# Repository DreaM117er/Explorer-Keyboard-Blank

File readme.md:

# Explorer Keyboard Blank 探索者3號

|4x6 v1|5x6 v1|
|--|--|
|||
|||
|||
|||

## 開發者前言

Plank，是大部分人入坑人體工學鍵盤時最常接觸到的鍵盤，因為它方且正，許多的人體工學鍵盤的基礎都是在這個方正的鍵盤上延伸；

Blank，翻譯成中文的意思為空白。結合了Plank所需要的基礎，進而把鍵盤拓展成可分離的版本，你可以只使用單側、也可以使用兩側、可以在你需要的那一側加裝自己需要的特殊元件，也可以將元件放置在手的左或右側...

並且支援Kailh矮軸Choc v1、v2、Gateron矮軸GLP雙熱插拔，選擇自己所喜歡的按鍵軸及鍵帽——

因此將它歸為探索者系列，稱之為Blank，稱之為3號。

## 靈感來源

- 我只是想做一把簡單的鍵盤。
- 開發上一把鍵盤時發現我最多只需要2顆旋鈕。
- 不想思考太多。
- 突然想到自己曾經在beekeeb上看到Cirque 40mm的觸控板模組。
- 試試看做個能同時翻面支援的電路板好了。

如果想知道完整的開發過程，請詳細閱讀[開發日誌](log.md)中的內文。

## 前置作業

### 電路板

||4x6 v1|5x6 v1|
|--|--|--|
|正面|||
|背面|||

### 外殼

||4x6 v1|5x6 v1|
|--|--|--|
|底板|||
|定位板|||
|擋板A|||
|擋板B|||
|擋板C|||
|MCU擋板|||

### 會使用到的工具

|名稱|備註|詳細說明|
|--|--|--|
|電烙鐵|-|焊錫、助焊劑等相關工具組|
|防靜電鑷子|-|用於微調貼片元件使用|
|金屬鑷子|-|用於測試電路用|
|加熱台|選配|用於固定貼片元件使用|
|熱風槍|選配|用於固定貼片元件使用|

### 使用材料（單側組裝）

|4x6 v1|5x6 v1|
|--|--|
|||
|||

|-|名稱|數量|數量|備註|詳細說明|
|--|--|--|--|--|--|
|||**4x6**|**5x6**|||
||PCB|1|-|-|雙面通用，`1.6mm`厚度|
||外殼|1|-|-|左右通用，`1.6mm`厚度|
|*|定位板|1|-|-|左右通用，`1.2mm`厚度|
|*|`ProMicro`|1|-|同腳MCU都可|推薦使用`RP2040`版本|
|*|二極體 `1N4148`|25|31|-|`SMD`貼片式|
|*|熱插拔座|24|30|`Choc`、`GLP`|二選一|
||`2pin`輕觸開關|1|-|-|-|
|*|M2螺絲墊片|6|-|-|穩固鍵盤結構使用|
||M2x`8mm` 扁頭螺絲|6|-|-|-|
||M2x`6mm` 扁頭螺絲|8|-|-|-|
||M2x`4mm` 扁頭螺絲|4|6|-|-|
||M2x`3mm` 扁頭螺絲|6|8|-|-|
||M2螺母|10|-|-|-|
||M2x`8mm` 雙通銅柱|2|4|-|-|
||M2x`5mm` 雙通銅柱|8|-|-|-|
||`ø8mm` `H1mm` 矽膠自黏腳貼|4|-|-|-|
|*|`Cirque` `40mm`觸控板|1|-|選配|推薦帶`曲面`之版本|
||`FFC` `12pin` 排線連接座|1|-|選配|如有`I2C轉接座`可不需使用|
|*|`FFC` `12pin` 軟排線|1|-|選配|`正對正接口`、`50mm`長即可|
|*|`4.7K` 上拉電阻|2|-|選配|`THT`直插式，安裝觸控板才需要使用|
|*|旋鈕編碼器|1|-|選配|`EC11`、`EC12`擇一使用；`L：10mm`、`A：4.5-5.0mm`，推薦`半軸` `D型`|
|*|旋鈕編碼器帽蓋|1|-|選配|`ø39mm`、`軸孔深4.5mm`特製版，推薦3D列印|
||`3.5mm` `TRRS`座|1|2|選配|單側安裝不需使用|

探索者3號支援各大網路商家販售的Cirque 40mm的觸控板模組拓展包，裡頭基本一應俱全，可考慮直接從通路購買：

- [40mm Cirque GlidePoint Circle Trackpad Module DIY Kit for Split Mechanical Keyboard](https://shop.beekeeb.com/product/40mm-cirque-glidepoint-circle-trackpad-module-diy-kit-for-split-mechanical-keyboard/)
- [GlidePoint Cirque Trackpad TM040040 TM035035](https://keycapsss.com/keyboard-parts/parts/211/glidepoint-cirque-trackpad-tm040040-tm035035)

### 注意事項

1. 上面表列材料表為`單片電路板安裝使用`。
2. 列表前標記`*`的材料為極度重要之零組件，請留意是否準備齊全，參照如下：

    - 二極體`1N4148`及`熱插拔座`請務必準備齊全，否則鍵盤會無法正常使用。
    - 旋鈕`編碼器`需搭配`帽蓋`一起安裝。
    - Crique 40mm`觸控板`需搭配`4.7k上拉電阻`、`12pin軟排線`安裝，缺一不可，請特別留意。
    - `M2螺絲墊片`務必準備齊全，有關鍵盤整體的`結構`，務必安裝上去。
 
3. 機械鍵軸務必跟隨熱插拔座的規格進行購買，因為`Choc跟GLP規格不相容`。
4. 使用電烙鐵時務必留意`環境通風`、`用電安全`及`燙傷預防`。
5. 在進入組裝環節之前，務必先將beekeeb及Keycapsss的組裝流程看過一輪：

    - [Cirque Trackpad i2c on Corne Keyboard Build Log](https://beekeeb.com/cirque-trackpad-i2c-on-corne-keyboard/)。
    - [GlidePoint Cirque Trackpad with Adapter PCB](https://keycapsss.com/help/cirque-trackpad/#spi-or-i2c)。

環境及材料都準備完畢之後，就可以開始進入[組裝環節](guide.md)了。

## 無私的感謝

### 工具軟體
- [KiCAD](https://www.kicad.org/) version `7.0.5`。
- [Autodesk Fusion](https://www.autodesk.com/products/fusion-360/free-trial)。
- [QMK](https://qmk.fm/)、[VIAL](https://get.vial.today/)。

### 規格書
- [TM040040 Trackpad](spc/TM040040.pdf)。
- [Resistor_THT](spc/Resistor_THT.png)。
- [molex 781271110 0.5 FPC CONN.](spc/FPC-Conn-781271110.pdf)。
- ALPS [EC11](<spc/Rotray Encoder EC11.pdf>)、[EC12E](<spc/Rotray Encoder EC12E.PDF>)。

### 商家及廠家
- [太豪股份有限公司](https://www.tai-hao.com/tw/)。
- [凱華電子有限公司](http://www.kailh.com/index.html)。
- [nuphy](https://nuphy.com/)及[Gateron](https://www.gateron.co/)。
- [beekeeb](https://shop.beekeeb.com/)。
- [Keycapsss](https://keycapsss.com/)。
- [JLCPCB](https://jlcpcb.com/)。

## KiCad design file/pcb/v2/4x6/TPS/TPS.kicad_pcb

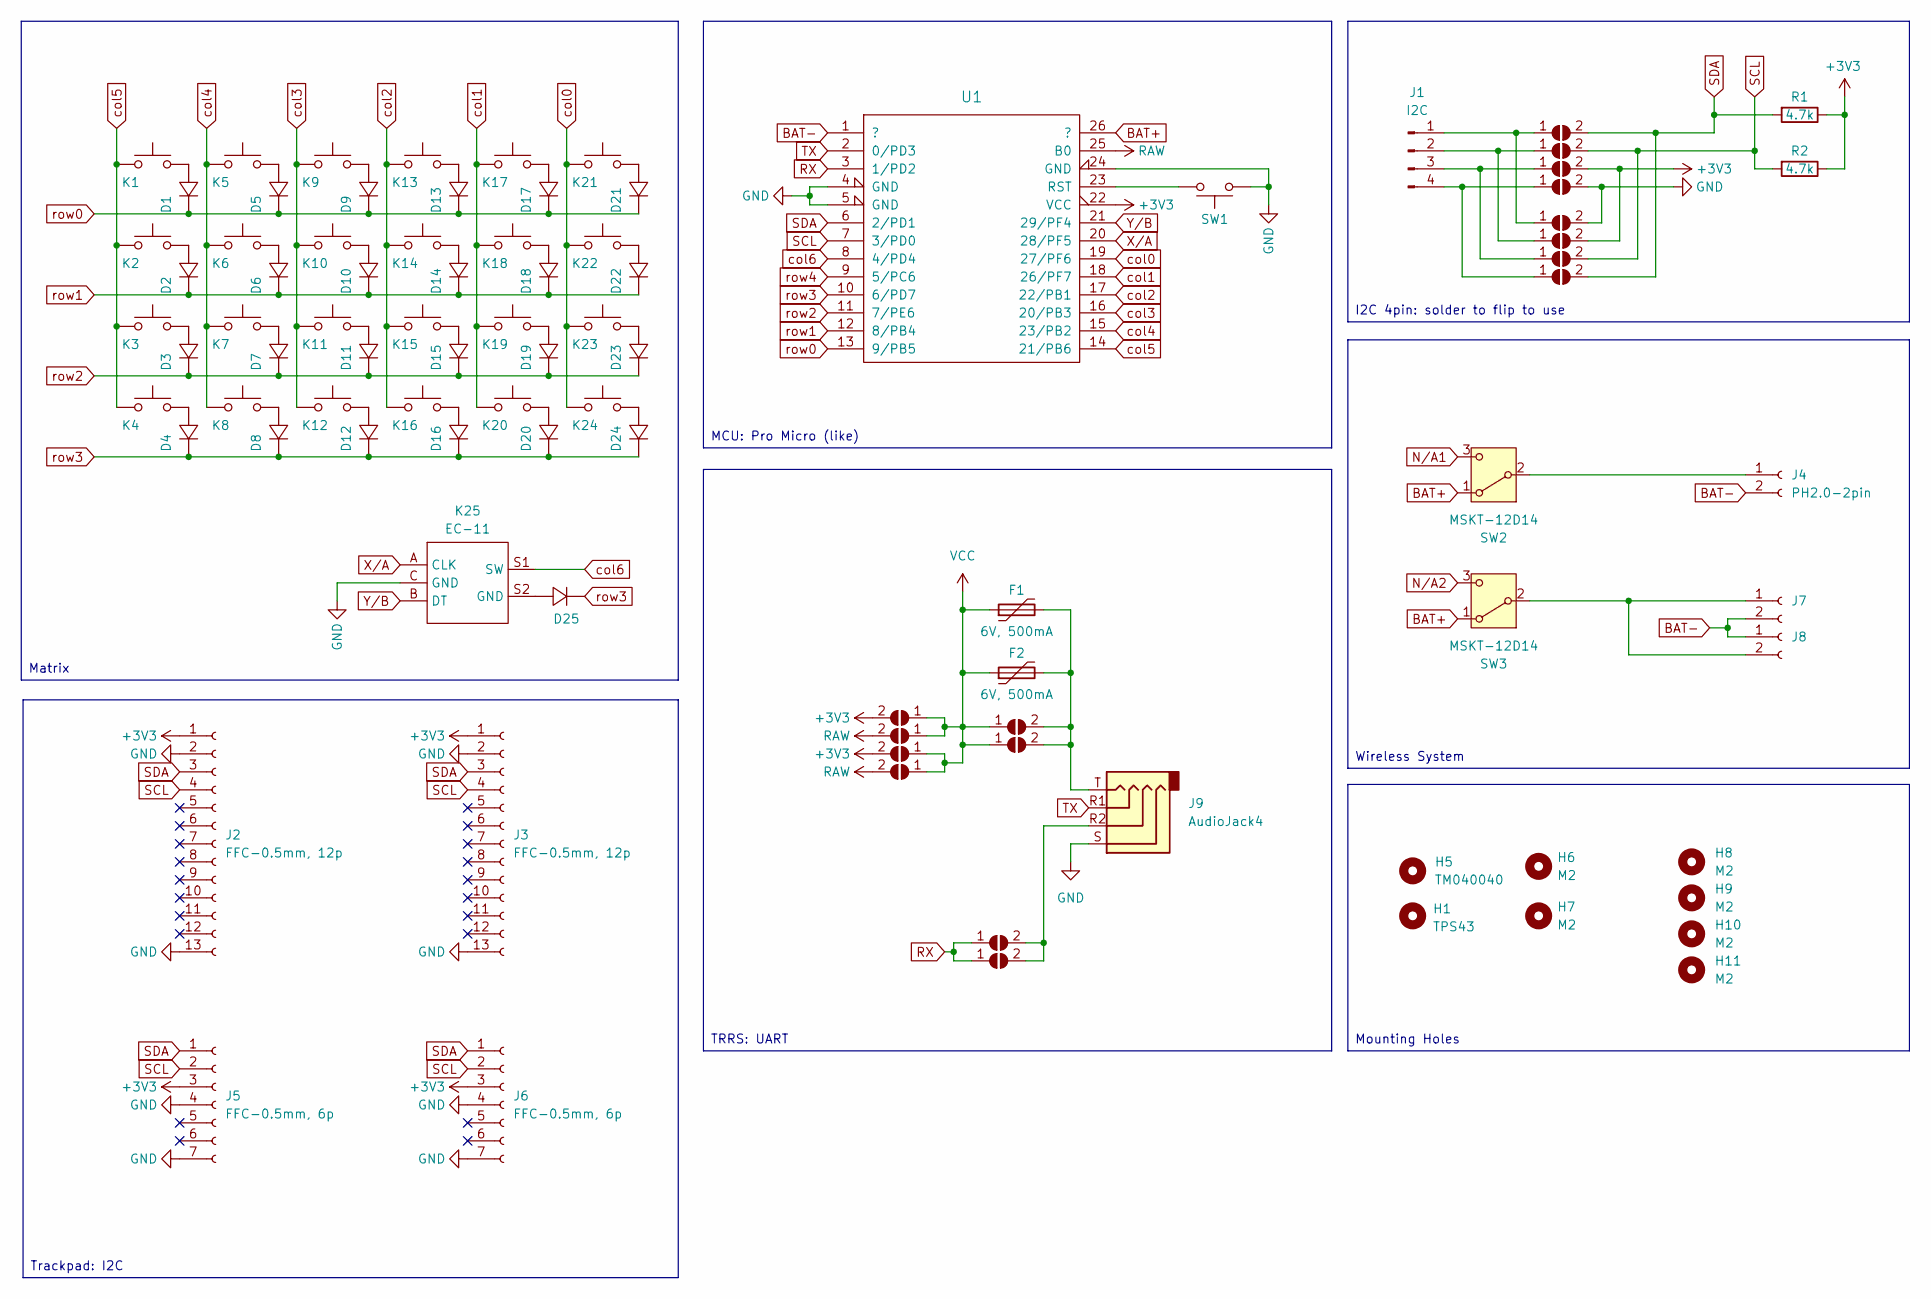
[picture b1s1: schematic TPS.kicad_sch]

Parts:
D1, D2, D3, D4, D5, D6, D7, D8, D9, D10, D11, D12, D13, D14, D15, D16, D17, D18, D19, D20, D21, D22, D23, D24, D25: 1N4148_SMD; D_SOD-123_handsolder_dual
F1, F2: 6V, 500mA; Fuse_0805_2012Metric
H1: TPS43; Azoteq_TPS43_201A_S
H5: TM040040; Trackpad_Cirque_TM040040
H6, H7, H8, H9, H10, H11: M2; MountingHole_2.2mm_M2
J1: I2C; PinHeader_1x04_P2.54mm_Vertical
J2, J3: FFC-0.5mm, 12p; Hirose_FH12-12S-0.5SH_1x12-1MP_P0.50mm_Horizontal
J4: PH2.0-2pin; JST_PH_S2B-PH-K_1x02_P2.00mm_Horizontal_dual
J5, J6: FFC-0.5mm, 6p; Hirose_FH12-6S-0.5SH_1x06-1MP_P0.50mm_Horizontal
J7, J8: PinHeader_1x02_P2.54mm_Vertical
J9: AudioJack4; TRRS-PJ-320A, dual side x2_3rd
JP1, JP2, JP3, JP4: PWR1; SolderJumper-2_P1.3mm_Open_Pad1.0x1.5mm
JP5, JP6, JP7, JP8, JP9, JP10, JP11, JP12: PWR1; SolderJumper-2_P1.3mm_Open_RoundedPad1.0x1.5mm
JP13, JP14: RX; SolderJumper-2_P1.3mm_Open_RoundedPad1.0x1.5mm
JP15, JP16: VCC; SolderJumper-2_P1.3mm_Open_Pad1.0x1.5mm
K1, K2, K3, K4, K5, K6, K7, K8, K9, K10, K11, K12, K13, K14, K15, K16, K17, K18, K19, K20, K21, K22, K23, K24: SW_Push; SW_Hotswap_KLP12_GLP3.0_MX_Plated_1.00u_Dualside
K25: EC-11; RotaryEncoder_EC11
R1, R2: 4.7k; R_Axial_DIN0204_L3.6mm_D1.6mm_P7.62mm_Horizontal
SW1: SW_Push; ResetSW_1side
SW2, SW3: MSKT-12D14; SW_SPDT_MSKT-12D14_SMD_dual
U1: MCU_ProMicro_13p; MCU_ProMicro_13p_dual

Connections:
+3V3: J2.1, J3.1, J5.3, J6.3, JP1.2 (B), JP3.2 (B), JP7.2 (B), JP10.2 (B), R1.1, R2.1, U1.22 (VCC)
BAT+: SW2.1 (A), SW3.1 (A), U1.26 (?)
BAT-: J4.2, J7.2, J8.1, U1.1 (?)
GND: J2.2, J2.13, J3.2, J3.13, J5.4, J5.7, J6.4, J6.7, J9.S, JP8.2 (B), JP9.2 (B), K25.C (GND), SW1.1, U1.4 (GND), U1.5 (GND), U1.24 (GND)
unnamed: D1.2, K1.2
unnamed: D2.2, K2.2
unnamed: D3.2, K3.2
unnamed: D4.2, K4.2
unnamed: D5.2, K5.2
unnamed: D6.2, K6.2
unnamed: D7.2, K7.2
unnamed: D8.2, K8.2
unnamed: D9.2, K9.2
unnamed: D10.2, K10.2
unnamed: D11.2, K11.2
unnamed: D12.2, K12.2
unnamed: D13.2, K13.2
unnamed: D14.2, K14.2
unnamed: D15.2, K15.2
unnamed: D16.2, K16.2
unnamed: D17.2, K17.2
unnamed: D18.2, K18.2
unnamed: D19.2, K19.2
unnamed: D20.2, K20.2
unnamed: D21.2, K21.2
unnamed: D22.2, K22.2
unnamed: D23.2, K23.2
unnamed: D24.2, K24.2
unnamed: D25.2, K25.S2 (GND)
unnamed: J1.1, JP5.1 (A), JP9.1 (A)
unnamed: J1.2, JP6.1 (A), JP10.1 (A)
unnamed: J1.3, JP7.1 (A), JP11.1 (A)
unnamed: J1.4, JP8.1 (A), JP12.1 (A)
unnamed: J4.1, SW2.2 (B)
unnamed: J7.1, J8.2, SW3.2 (B)
unnamed: J9.R2, JP13.2 (B), JP14.2 (B)
unnamed: F1.2, F2.2, J9.T, JP15.2 (B), JP16.2 (B)
unnamed: SW1.2, U1.23 (RST)
N/A1: SW2.3 (C)
N/A2: SW3.3 (C)
RAW: JP2.2 (B), JP4.2 (B), U1.25 (B0)
RX: JP13.1 (A), JP14.1 (A), U1.3 (1/PD2)
SCL: J2.4, J3.4, J5.2, J6.2, JP6.2 (B), JP11.2 (B), R2.2, U1.7 (3/PD0)
SDA: J2.3, J3.3, J5.1, J6.1, JP5.2 (B), JP12.2 (B), R1.2, U1.6 (2/PD1)
TX: J9.R1, U1.2 (0/PD3)
VCC: F1.1, F2.1, JP1.1 (A), JP2.1 (A), JP3.1 (A), JP4.1 (A), JP15.1 (A), JP16.1 (A)
X/A: K25.A (CLK), U1.20 (28/PF5)
Y/B: K25.B (DT), U1.21 (29/PF4)
col0: K21.1, K22.1, K23.1, K24.1, U1.19 (27/PF6)
col1: K17.1, K18.1, K19.1, K20.1, U1.18 (26/PF7)
col2: K13.1, K14.1, K15.1, K16.1, U1.17 (22/PB1)
col3: K9.1, K10.1, K11.1, K12.1, U1.16 (20/PB3)
col4: K5.1, K6.1, K7.1, K8.1, U1.15 (23/PB2)
col5: K1.1, K2.1, K3.1, K4.1, U1.14 (21/PB6)
col6: K25.S1 (SW), U1.8 (4/PD4)
row0: D1.1, D5.1, D9.1, D13.1, D17.1, D21.1, U1.13 (9/PB5)
row1: D2.1, D6.1, D10.1, D14.1, D18.1, D22.1, U1.12 (8/PB4)
row2: D3.1, D7.1, D11.1, D15.1, D19.1, D23.1, U1.11 (7/PE6)
row3: D4.1, D8.1, D12.1, D16.1, D20.1, D24.1, D25.1, U1.10 (6/PD7)
row4: U1.9 (5/PC6)

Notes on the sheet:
I2C 4pin: solder to flip to use
Trackpad: I2C
Mounting Holes
TRRS: UART
Wireless System
MCU: Pro Micro (like)
Matrix

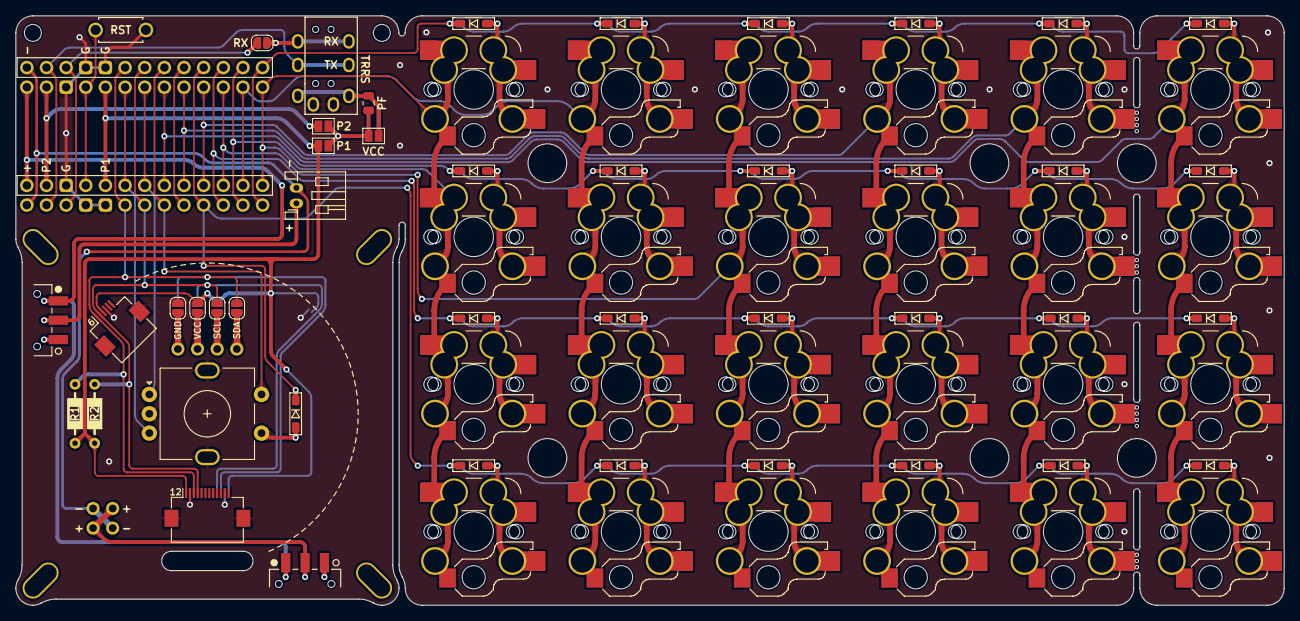
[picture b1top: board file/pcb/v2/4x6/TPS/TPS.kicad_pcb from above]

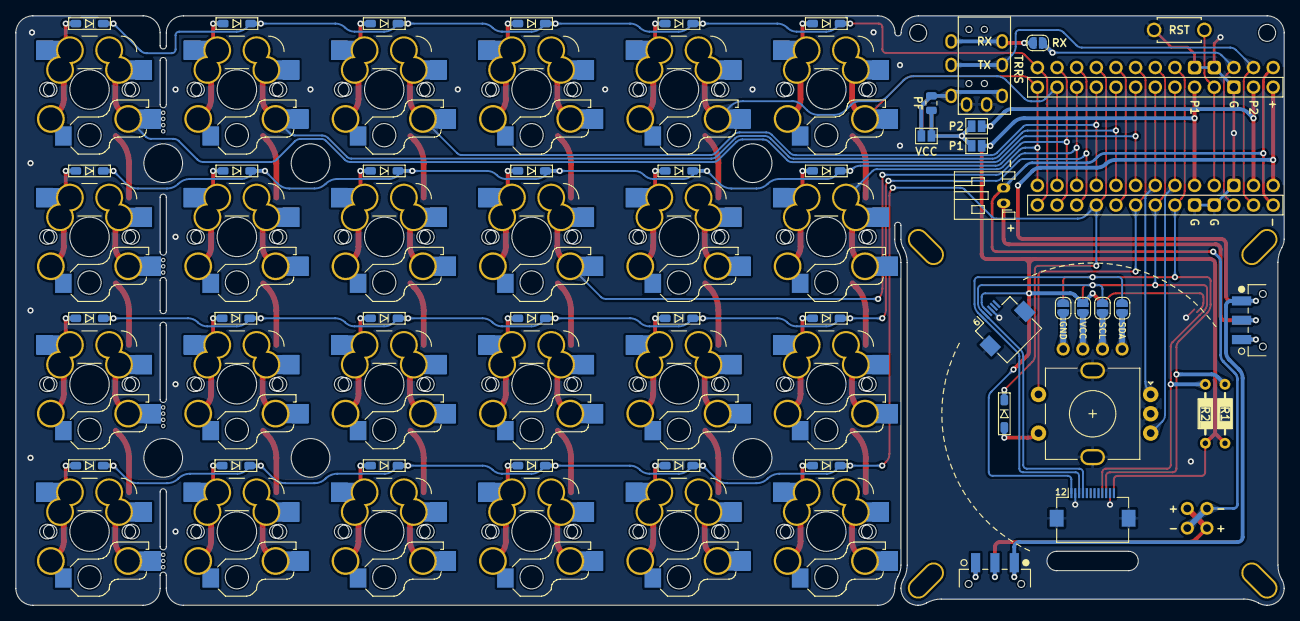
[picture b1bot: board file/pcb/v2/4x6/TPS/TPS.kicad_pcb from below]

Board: 2 copper layers, 164.0 x 76.2 mm, 95 parts (12 on the bottom side), 57 nets.

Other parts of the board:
H14, H15, H16, H17: edge; Breakaway_Tabs_2

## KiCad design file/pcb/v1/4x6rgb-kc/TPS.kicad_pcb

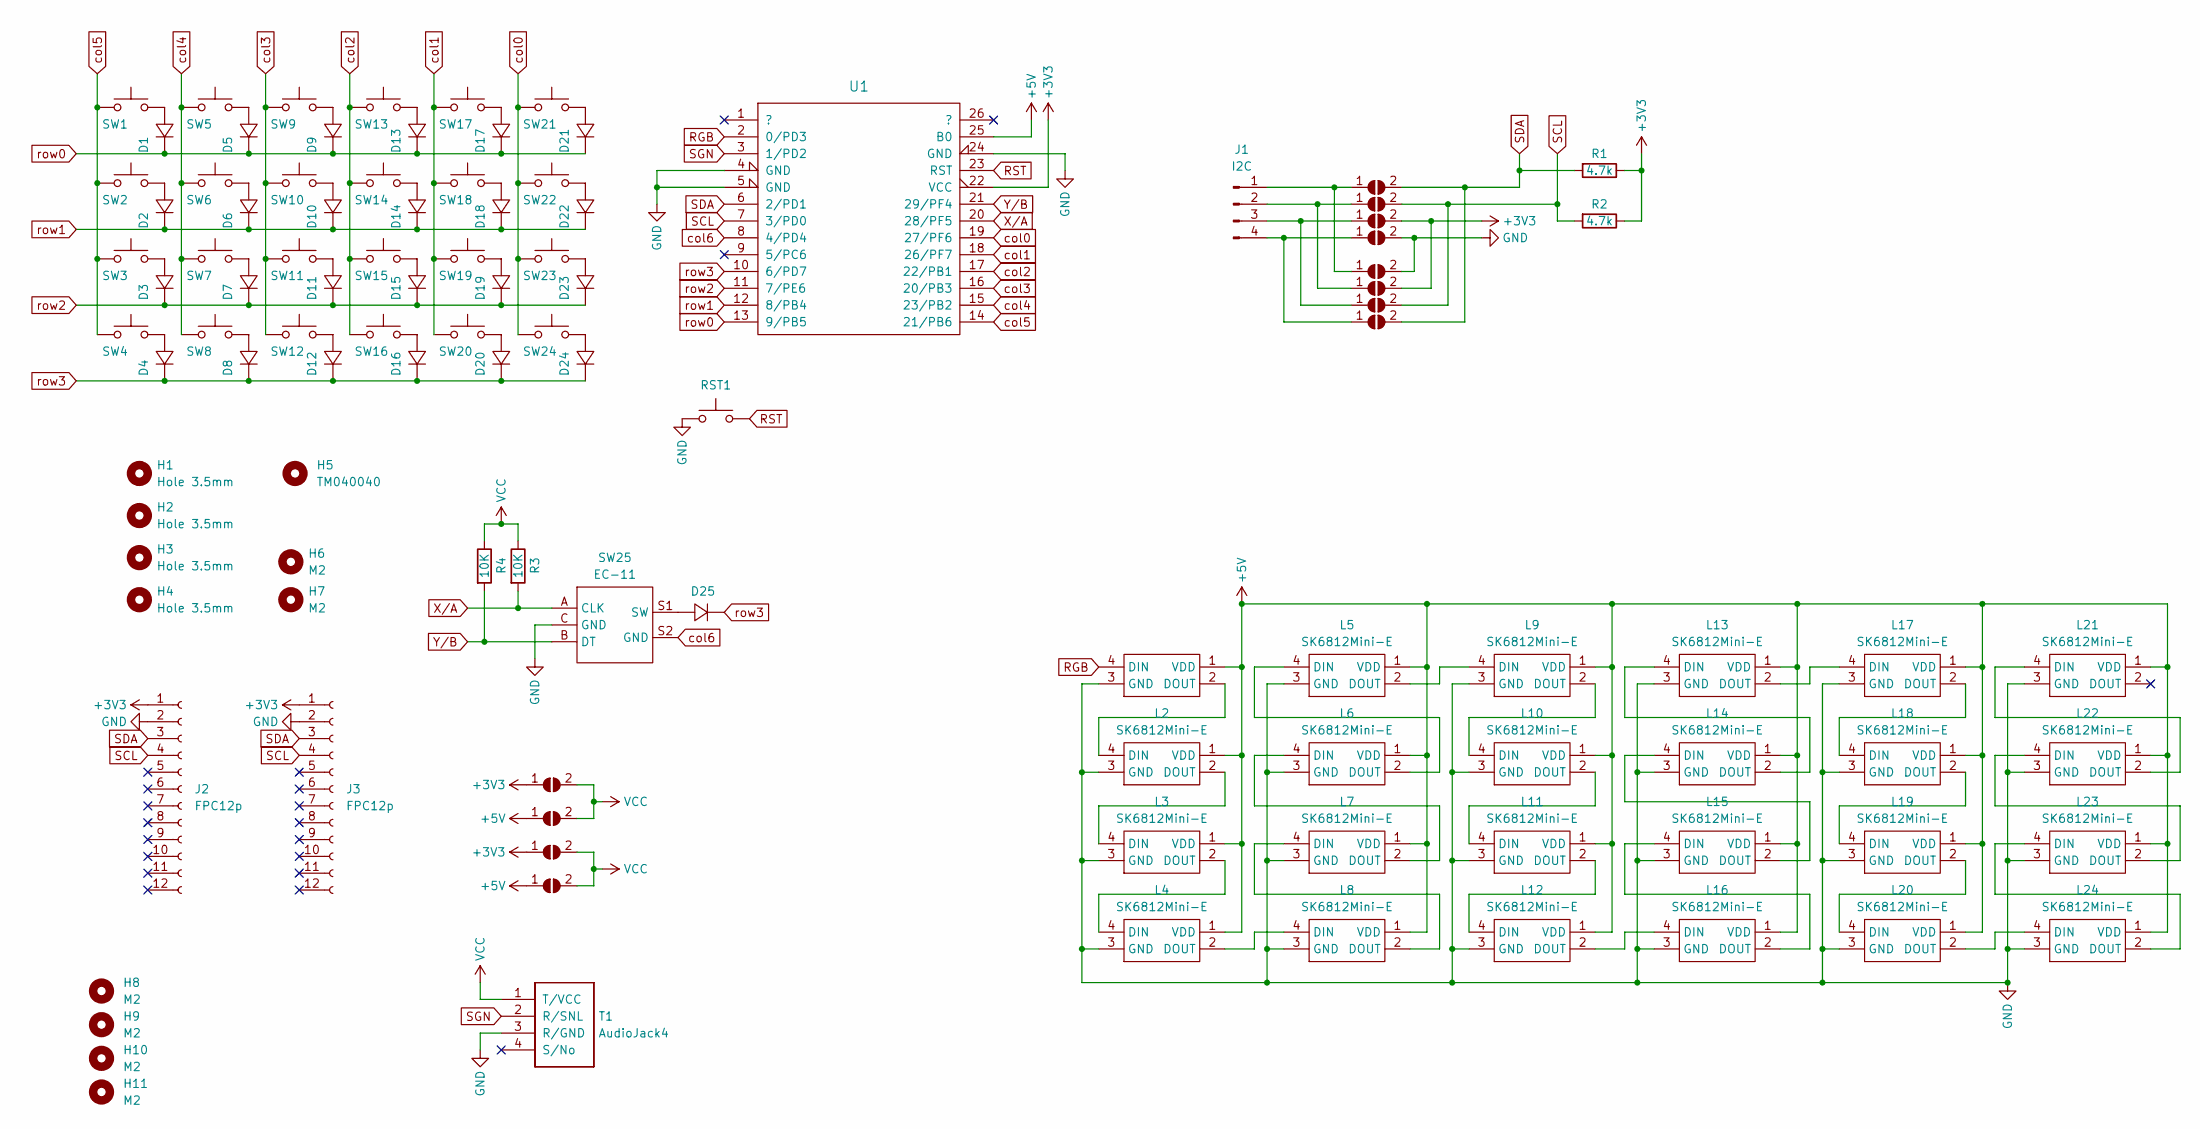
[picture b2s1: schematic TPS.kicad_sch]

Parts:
D1, D2, D3, D4, D5, D6, D7, D8, D9, D10, D11, D12, D13, D14, D15, D16, D17, D18, D19, D20, D21, D22, D23, D24, D25: 1N4148_SMD; D_SOD-123_dual
H1, H2, H3, H4: Hole 3.5mm; MountingHole_3.5mm
H5: TM040040; Trackpad_Cirque_TM040040
H6, H7, H8, H9, H10, H11: M2; MountingHole_2.2mm_M2
J1: I2C; PinHeader_1x04_P2.54mm_Vertical
J2, J3: FPC12p; Hirose_FH12-12S-0.5SH_1x12-1MP_P0.50mm_Horizontal
JP1, JP2, JP3, JP4: PWR1; SolderJumper-2_P1.3mm_Open_Pad1.0x1.5mm
JP5, JP6, JP7, JP8, JP9, JP10, JP11, JP12: PWR1; SolderJumper-2_P1.3mm_Open_RoundedPad1.0x1.5mm
L1, L2, L3, L4, L5, L6, L7, L8, L9, L10, L11, L12, L13, L14, L15, L16, L17, L18, L19, L20, L21, L22, L23, L24: SK6812Mini-E; LED_SK6812MINI-E_dual
R1, R2: 4.7k; R_Axial_DIN0204_L3.6mm_D1.6mm_P7.62mm_Horizontal
R3, R4: 10K; R_Axial_DIN0204_L3.6mm_D1.6mm_P7.62mm_Horizontal
RST1: SW_Push; ResetSW_1side
SW1, SW2, SW3, SW4, SW5, SW6, SW7, SW8, SW9, SW10, SW11, SW12, SW13, SW14, SW15, SW16, SW17, SW18, SW19, SW20, SW21, SW22, SW23, SW24: SW_Push; SW_Choc_KLP12_Hotswap_1.00u_dual
SW25: EC-11; RotaryEncoder_EC11
T1: AudioJack4; TRRS-PJ-320A, dual side x2
U1: MCU_ProMicro_13p; MCU_ProMicro_13p_dual

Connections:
+3V3: J2.1, J3.1, JP1.1 (A), JP3.1 (A), JP7.2 (B), JP10.2 (B), R1.1, R2.1, U1.22 (VCC)
+5V: JP2.1 (A), JP4.1 (A), L1.1 (VDD), L2.1 (VDD), L3.1 (VDD), L4.1 (VDD), L5.1 (VDD), L6.1 (VDD), L7.1 (VDD), L8.1 (VDD), L9.1 (VDD), L10.1 (VDD), L11.1 (VDD), L12.1 (VDD), L13.1 (VDD), L14.1 (VDD), L15.1 (VDD), L16.1 (VDD), L17.1 (VDD), L18.1 (VDD), L19.1 (VDD), L20.1 (VDD), L21.1 (VDD), L22.1 (VDD), L23.1 (VDD), L24.1 (VDD), U1.25 (B0)
GND: J2.2, J3.2, JP8.2 (B), JP9.2 (B), L1.3 (GND), L2.3 (GND), L3.3 (GND), L4.3 (GND), L5.3 (GND), L6.3 (GND), L7.3 (GND), L8.3 (GND), L9.3 (GND), L10.3 (GND), L11.3 (GND), L12.3 (GND), L13.3 (GND), L14.3 (GND), L15.3 (GND), L16.3 (GND), L17.3 (GND), L18.3 (GND), L19.3 (GND), L20.3 (GND), L21.3 (GND), L22.3 (GND), L23.3 (GND), L24.3 (GND), RST1.1, SW25.C (GND), T1.3 (R/GND), U1.4 (GND), U1.5 (GND), U1.24 (GND)
unnamed: D1.2, SW1.2
unnamed: D2.2, SW2.2
unnamed: D3.2, SW3.2
unnamed: D4.2, SW4.2
unnamed: D5.2, SW5.2
unnamed: D6.2, SW6.2
unnamed: D7.2, SW7.2
unnamed: D8.2, SW8.2
unnamed: D9.2, SW9.2
unnamed: D10.2, SW10.2
unnamed: D11.2, SW11.2
unnamed: D12.2, SW12.2
unnamed: D13.2, SW13.2
unnamed: D14.2, SW14.2
unnamed: D15.2, SW15.2
unnamed: D16.2, SW16.2
unnamed: D17.2, SW17.2
unnamed: D18.2, SW18.2
unnamed: D19.2, SW19.2
unnamed: D20.2, SW20.2
unnamed: D21.2, SW21.2
unnamed: D22.2, SW22.2
unnamed: D23.2, SW23.2
unnamed: D24.2, SW24.2
unnamed: J1.1, JP5.1 (A), JP9.1 (A)
unnamed: J1.2, JP6.1 (A), JP10.1 (A)
unnamed: J1.3, JP7.1 (A), JP11.1 (A)
unnamed: J1.4, JP8.1 (A), JP12.1 (A)
unnamed: L1.2 (DOUT), L2.4 (DIN)
unnamed: L2.2 (DOUT), L3.4 (DIN)
unnamed: L3.2 (DOUT), L4.4 (DIN)
unnamed: L4.2 (DOUT), L8.4 (DIN)
unnamed: L5.4 (DIN), L6.2 (DOUT)
unnamed: L5.2 (DOUT), L9.4 (DIN)
unnamed: L6.4 (DIN), L7.2 (DOUT)
unnamed: L7.4 (DIN), L8.2 (DOUT)
unnamed: L9.2 (DOUT), L10.4 (DIN)
unnamed: L10.2 (DOUT), L11.4 (DIN)
unnamed: L11.2 (DOUT), L12.4 (DIN)
unnamed: L12.2 (DOUT), L16.4 (DIN)
unnamed: L13.4 (DIN), L14.2 (DOUT)
unnamed: L13.2 (DOUT), L17.4 (DIN)
unnamed: L14.4 (DIN), L15.2 (DOUT)
unnamed: L15.4 (DIN), L16.2 (DOUT)
unnamed: L17.2 (DOUT), L18.4 (DIN)
unnamed: L18.2 (DOUT), L19.4 (DIN)
unnamed: L19.2 (DOUT), L20.4 (DIN)
unnamed: L20.2 (DOUT), L24.4 (DIN)
unnamed: L21.4 (DIN), L22.2 (DOUT)
unnamed: L22.4 (DIN), L23.2 (DOUT)
unnamed: L23.4 (DIN), L24.2 (DOUT)
unnamed: D25.2, SW25.S1 (SW)
RGB: L1.4 (DIN), U1.2 (0/PD3)
RST: RST1.2, U1.23 (RST)
SCL: J2.4, J3.4, JP6.2 (B), JP11.2 (B), R2.2, U1.7 (3/PD0)
SDA: J2.3, J3.3, JP5.2 (B), JP12.2 (B), R1.2, U1.6 (2/PD1)
SGN: T1.2 (R/SNL), U1.3 (1/PD2)
VCC: JP1.2 (B), JP2.2 (B), JP3.2 (B), JP4.2 (B), R3.1, R4.1, T1.1 (T/VCC)
X/A: R3.2, SW25.A (CLK), U1.20 (28/PF5)
Y/B: R4.2, SW25.B (DT), U1.21 (29/PF4)
col0: SW21.1, SW22.1, SW23.1, SW24.1, U1.19 (27/PF6)
col1: SW17.1, SW18.1, SW19.1, SW20.1, U1.18 (26/PF7)
col2: SW13.1, SW14.1, SW15.1, SW16.1, U1.17 (22/PB1)
col3: SW9.1, SW10.1, SW11.1, SW12.1, U1.16 (20/PB3)
col4: SW5.1, SW6.1, SW7.1, SW8.1, U1.15 (23/PB2)
col5: SW1.1, SW2.1, SW3.1, SW4.1, U1.14 (21/PB6)
col6: SW25.S2 (GND), U1.8 (4/PD4)
row0: D1.1, D5.1, D9.1, D13.1, D17.1, D21.1, U1.13 (9/PB5)
row1: D2.1, D6.1, D10.1, D14.1, D18.1, D22.1, U1.12 (8/PB4)
row2: D3.1, D7.1, D11.1, D15.1, D19.1, D23.1, U1.11 (7/PE6)
row3: D4.1, D8.1, D12.1, D16.1, D20.1, D24.1, D25.1, U1.10 (6/PD7)

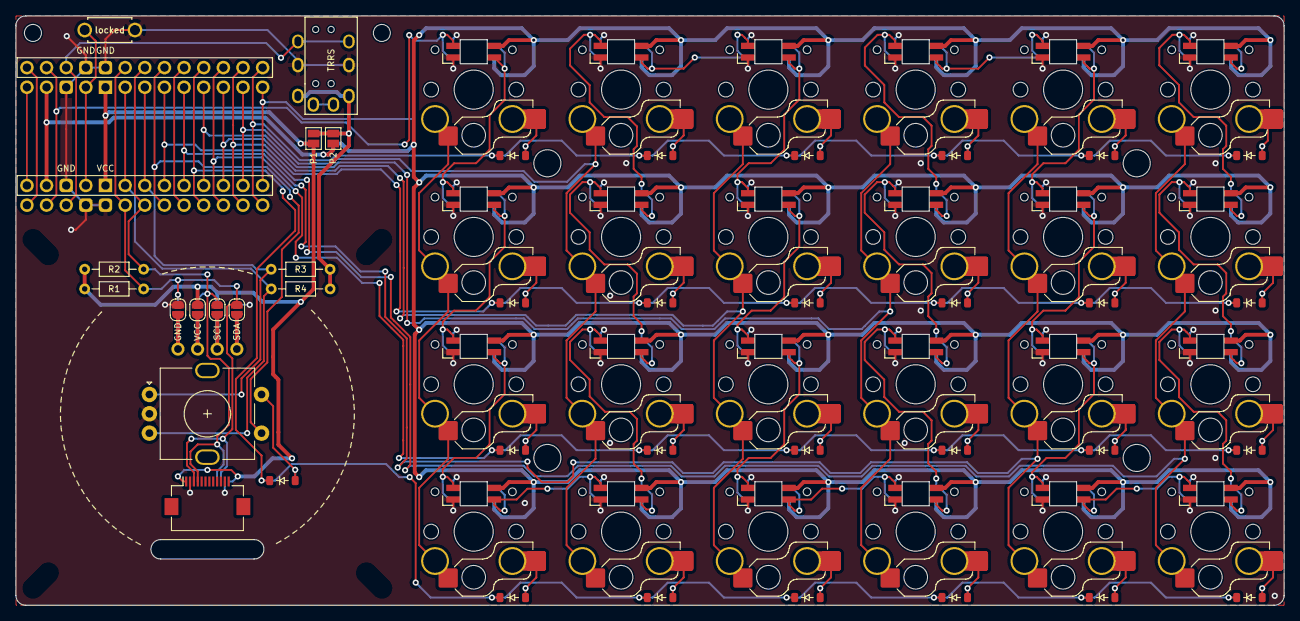
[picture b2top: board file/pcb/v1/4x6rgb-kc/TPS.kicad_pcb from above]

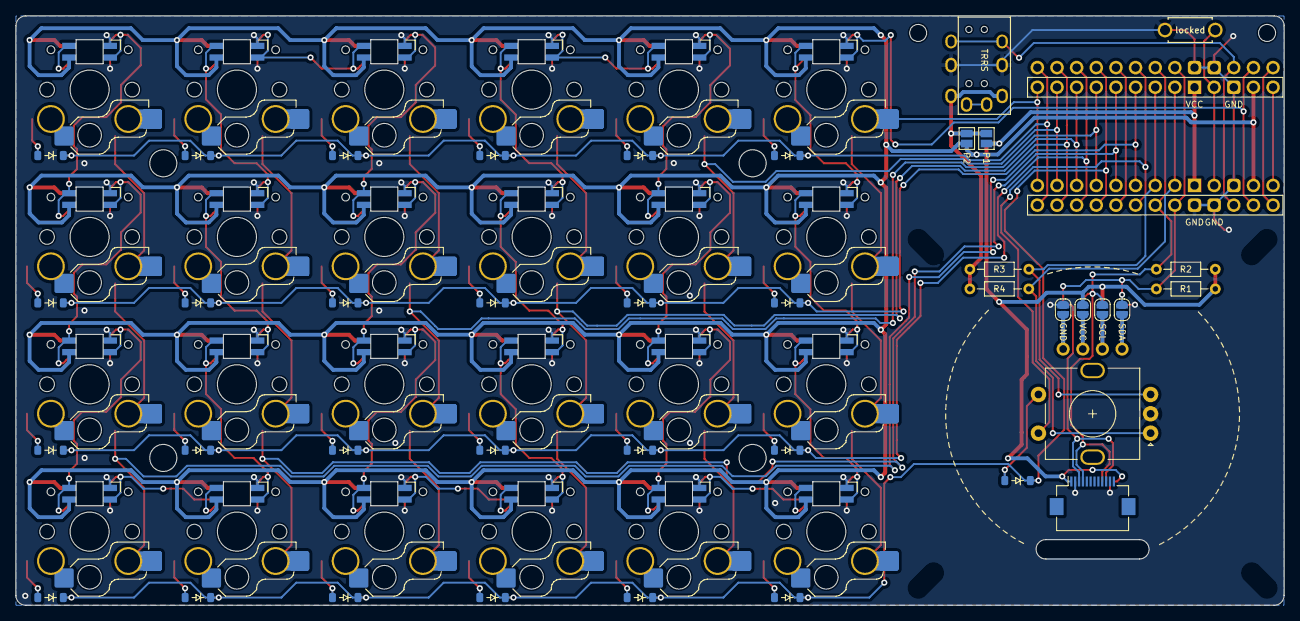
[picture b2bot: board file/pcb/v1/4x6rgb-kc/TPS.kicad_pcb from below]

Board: 2 copper layers, 164.0 x 76.2 mm, 107 parts (32 on the bottom side), 74 nets.

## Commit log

2024-08-15 update spc
2024-08-17 update t8
2024-08-17 update pcb&step
2024-08-17 update info
2024-08-18 update guide pic
2024-08-22 update en guide
2024-11-06 fix thickness of the plate
2024-11-06 update v1 5x6 version
2024-11-07 update 5x6 json for fit 4x6 & 5x6
2024-11-16 update readme.md 5x6
2024-11-16 renew 4x6 5x6 info
2024-11-16 renew list
2024-11-16 update 5x6 pics & list
2024-11-16 update 5x6 list
2025-01-26 update blank-kc rgb pcb
2025-01-28 remove blankrgb pcb files
2025-10-31 clean file and upload v2
2025-10-31 upload v2
2025-10-31 fix v2 bottom case
2025-11-01 fix v2 bom list
2025-11-02 add TPS43 module
2025-11-02 upload v2 3d files
2025-11-03 upload 5x6 case
2025-11-03 upload all layout pics
2025-11-04 fix 5x6 PCB
2025-11-04 fix 5x6 Plate
2025-11-04 fix plate
2025-11-20 fix TRRS TX/RX pins
2025-12-14 fix main PCB file UI
2025-12-21 add 4x6info pic
